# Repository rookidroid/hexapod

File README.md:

#  Hexapod

A family of 18-DOF, 3D-printed hexapod robots powered by an ESP32. Walk them from your phone over WiFi, or stream poses to them live from a computer. All the robots run the same firmware and gait generator. What differs is their frame, servos and dimensions.

## The Robots

| | [Nougat](./robots/nougat/) | [Mochi](./robots/mochi/) | [Macaroon](./robots/macaroon/) |
|---|---|---|---|
| |  |  |  |
| **Servos** | 18 × 21G digital | 18 × MG92B micro | 18 × 25 kg digital |
| **Battery** | 2 × 18650 (2S1P) | 2 × 18650 (2S) | 4 × 18650 (2S2P) |
| **Leg links** (coxa / femur / tibia) | 38 / 54 / 97 mm | 36 / 44 / 85 mm | 62 / 76 / 132 mm |
| **Controller** | ESP32 (Pico W legacy) | ESP32 (Pico W legacy) | ESP32 |
| **Firmware define** | `ROBOT_NOUGAT` | `ROBOT_MOCHI` | `ROBOT_MACAROON` |
| **WiFi SSID** | `hexapod_nougat` | `hexapod` | `hexapod_macaroon` |

Each robot's folder has its full build guide: bill of materials, 3D-printed parts, assembly, software setup, calibration and troubleshooting.

## Repository Layout

```text
hexapod/
├── robots/                 # Hardware for each robot
│   ├── nougat/             #   README (build guide), 3d print/, images/
│   ├── mochi/
│   └── macaroon/
├── images/                 # Images shared by all robots
└── software/
    ├── hexapod_esp32/      # ESP32 firmware (Arduino sketch), shared by all robots
    │   ├── robot.h         #   Pick the robot you are building here
    │   └── src/robots/     #   Per-robot settings and generated motion tables
    ├── package_esp32.py    # Packages the ESP32 sketch into one copy per robot
    ├── hexapod_pico/       # Legacy Raspberry Pi Pico firmware (unmaintained)
    └── path_tool/          # Gait generator that produces the motion tables
        └── robots/         #   Per-robot geometry and gait parameters (JSON)
```

## Quick Start

1. Build the robot by following its guide in [`robots/`](./robots/).
2. Open [`software/hexapod_esp32/hexapod_esp32.ino`](./software/hexapod_esp32/hexapod_esp32.ino) in the Arduino IDE.
3. In [`robot.h`](./software/hexapod_esp32/robot.h), leave only your robot's `#define ROBOT_*` uncommented.
4. Upload, join the robot's WiFi network and calibrate it at `http://192.168.4.1`.

To skip step 3, download `hexapod_<robot>_<version>.zip` from the [releases](https://github.com/rookidroid/hexapod/releases): a copy of the sketch with your robot already selected. `python software/package_esp32.py` builds the same zips locally into `dist/`.

The [ESP32 firmware README](./software/hexapod_esp32/README.md) covers setup, the UDP protocol and OTA updates. The [path tool README](./software/path_tool/README.md) explains how the motion tables are generated and how to add a new robot.

## License

[GPL-3.0](./LICENSE)

## Support

- Website: [rookidroid.com](https://rookidroid.com/)
- Issues: [GitHub Issues](https://github.com/rookidroid/hexapod/issues)
- E-mail: [info@rookidroid.com](mailto:info@rookidroid.com)

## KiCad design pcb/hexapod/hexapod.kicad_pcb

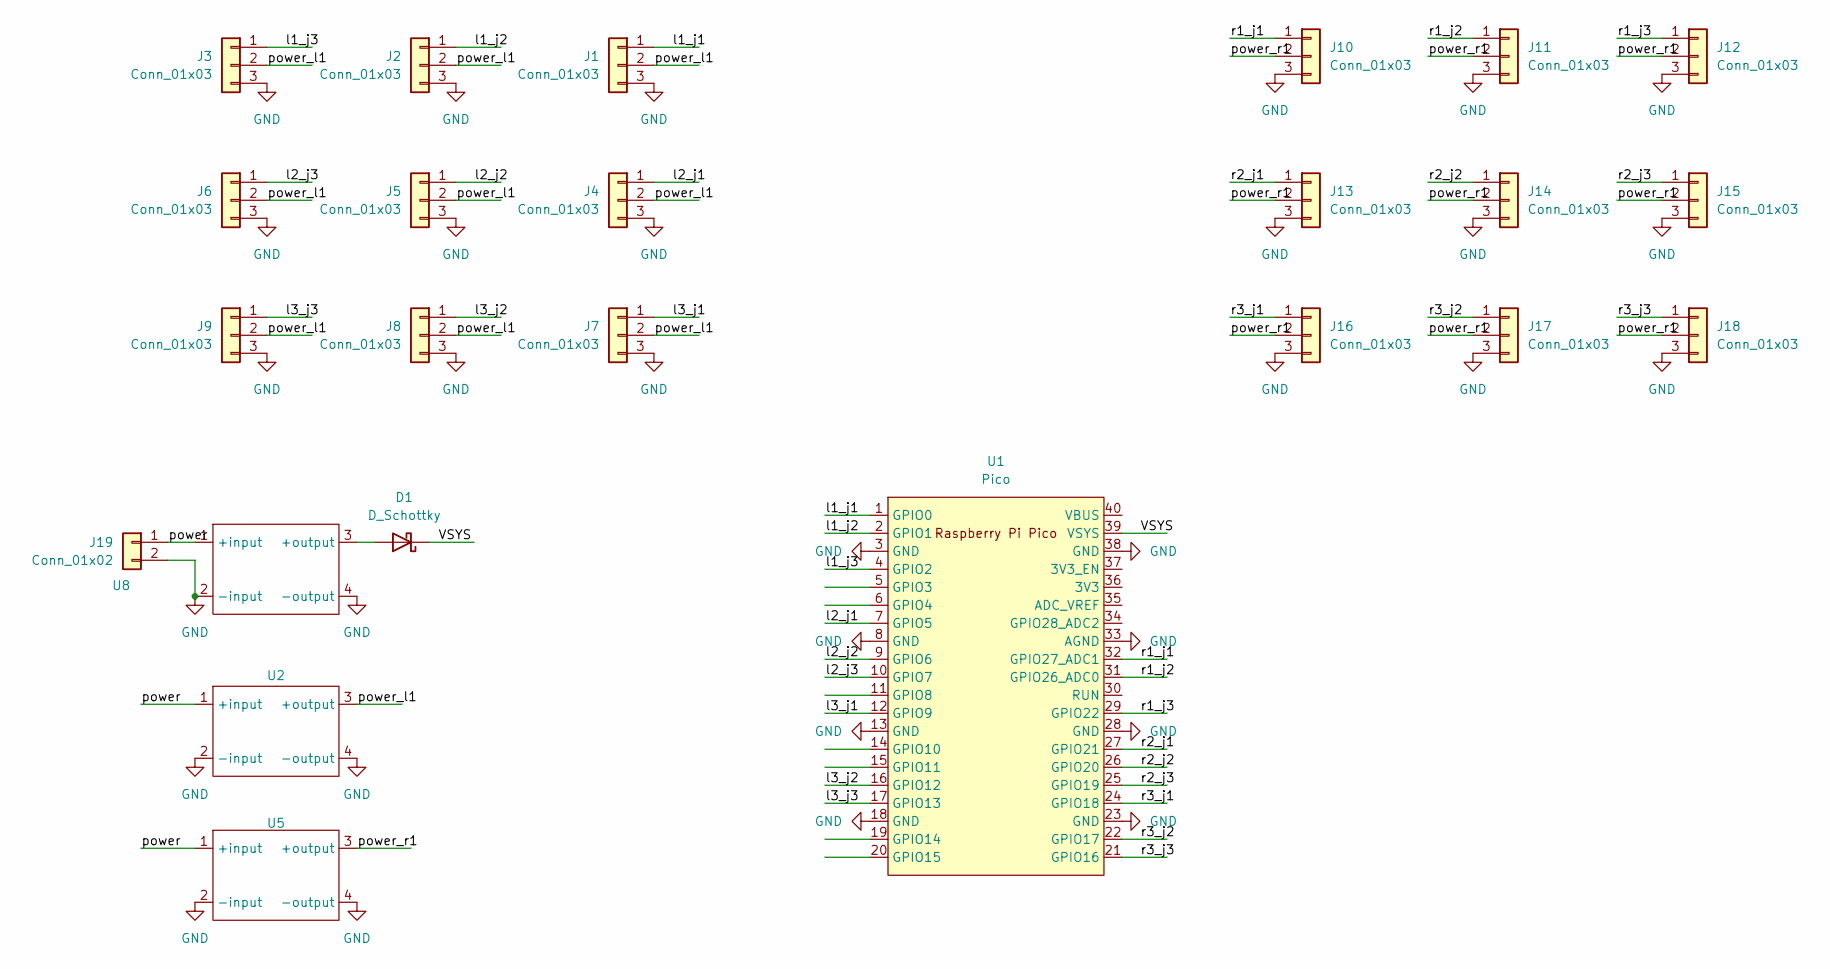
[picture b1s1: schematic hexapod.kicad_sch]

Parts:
D1: D_Schottky; D_T-1_P10.16mm_Horizontal
J1, J2, J3, J4, J5, J6, J7, J8, J9, J10, J11, J12, J13, J14, J15, J16, J17, J18: Conn_01x03; PinHeader_1x03_P2.54mm_Vertical
J19: Conn_01x02; TerminalBlock_MaiXu_MX126-5.0-02P_1x02_P5.00mm
U1: Pico; RPi_Pico_SMD_TH
U2, U5: XL4005
U8: Mini360

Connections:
/VSYS: D1.1 (K), U1.39 (VSYS)
/l1_j1: J1.1, U1.1 (GPIO0)
/l1_j2: J2.1, U1.2 (GPIO1)
/l1_j3: J3.1, U1.4 (GPIO2)
/l2_j1: J4.1, U1.7 (GPIO5)
/l2_j2: J5.1, U1.9 (GPIO6)
/l2_j3: J6.1, U1.10 (GPIO7)
/l3_j1: J7.1, U1.12 (GPIO9)
/l3_j2: J8.1, U1.16 (GPIO12)
/l3_j3: J9.1, U1.17 (GPIO13)
/power: J19.1, U2.1 (+input), U5.1 (+input), U8.1 (+input)
/power_l1: J1.2, J2.2, J3.2, J4.2, J5.2, J6.2, J7.2, J8.2, J9.2, U2.3 (+output)
/power_r1: J10.2, J11.2, J12.2, J13.2, J14.2, J15.2, J16.2, J17.2, J18.2, U5.3 (+output)
/r1_j1: J10.1, U1.32 (GPIO27_ADC1)
/r1_j2: J11.1, U1.31 (GPIO26_ADC0)
/r1_j3: J12.1, U1.29 (GPIO22)
/r2_j1: J13.1, U1.27 (GPIO21)
/r2_j2: J14.1, U1.26 (GPIO20)
/r2_j3: J15.1, U1.25 (GPIO19)
/r3_j1: J16.1, U1.24 (GPIO18)
/r3_j2: J17.1, U1.22 (GPIO17)
/r3_j3: J18.1, U1.21 (GPIO16)
GND: J1.3, J2.3, J3.3, J4.3, J5.3, J6.3, J7.3, J8.3, J9.3, J10.3, J11.3, J12.3, J13.3, J14.3, J15.3, J16.3, J17.3, J18.3, J19.2, U1.3 (GND), U1.8 (GND), U1.13 (GND), U1.18 (GND), U1.23 (GND), U1.28 (GND), U1.33 (AGND), U1.38 (GND), U2.2 (-input), U2.4 (-output), U5.2 (-input), U5.4 (-output), U8.2 (-input), U8.4 (-output)
unnamed: D1.2 (A), U8.3 (+output)

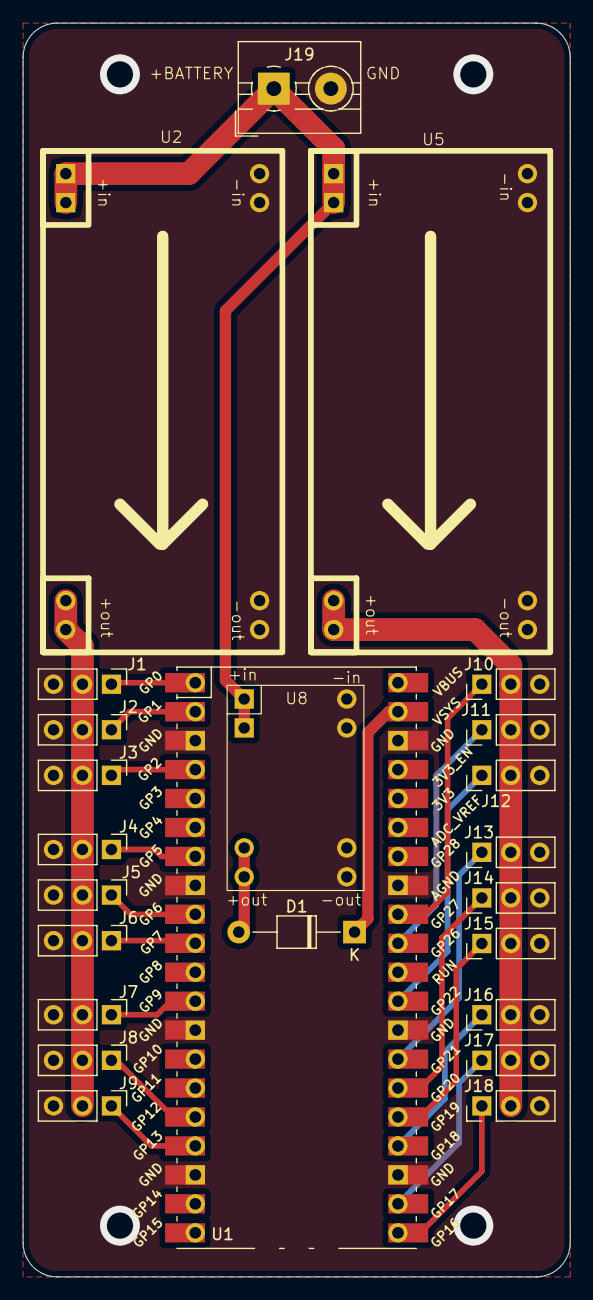
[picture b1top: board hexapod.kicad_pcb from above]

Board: 2 copper layers, 48.0 x 110.0 mm, 24 parts (0 on the bottom side), 24 nets.

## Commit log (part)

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2024-06-20 update path generator
2024-07-02 move configurations to config.h
2024-07-02 rename
2024-09-11 v1.0
2024-09-24 adjust leg for MG90S
2024-09-28 update lut for the leg adjustment
2024-10-04 update instruction
2024-10-05 update docs
2024-10-07 photo of mg90s
2024-10-13 #1 Correct schematic mistakes
2024-10-14 #2 Improve readme for mirrored joints and feet
2024-11-10 remove android
2024-12-17 pcb design
2024-12-18 change default IP
2024-12-18 gerber file for fab
2024-12-29 remove old stl
2025-01-03 update Mini360 pad
2025-01-05 fix pcb
2025-01-11 move pcb to another repo
2025-02-22 add body models
2025-02-22 adding foot and joint model files
2025-02-22 add leg model files
2025-02-22 update gifs
2025-02-22 add diagram
2025-02-22 add servo image
2025-02-23 add controller boards
2025-02-24 update diagrams
2025-02-24 add photos
2025-02-24 improve images
2025-02-24 remove photos
2025-02-25 new images
2025-03-01 update photos
2025-05-29 add a flag to set calibration mode
2025-11-23 Refactor hexapod initialization and command parsing
    Improves code organization by extracting UDP command parsing into a dedicated function, adds helper for setting all servo positions, and introduces constants for hardware configuration. Enhances seri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
2025-11-23 Delay boot sequence until WiFi client connects
    The boot-up motion now waits for a WiFi client to connect before executing. This ensures the hexapod only starts its boot sequence when a client is present, and allows OTA updates during the wait. If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
2025-11-24 Refactor formatting and improve code consistency
    This commit updates spacing, indentation, and formatting throughout hexapod_esp32.ino for improved readability and consistency. No functional changes were made; only code style and formatting adjustm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
2025-11-24 Refactor motion command handling with unified config
    Introduced a MotionConfig struct and array to unify motion command mapping and LUT selection. Replaced repetitive if-else chains in loop() and parseCommand() with table-driven lookups, improving main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
2025-11-24 Add detailed comments and structure to hexapod_esp32.ino
    Improved code readability by adding descriptive comments, section headers, and clarifying variable purposes throughout the hexapod_esp32.ino file. Enhanced documentation for motion configuration, har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
2025-11-24 Refactor motion mode handling to use indices
    Removed MotionMode enum and updated motion configuration to map commands directly to LUTs using table indices. Simplified motion state tracking and execution logic by replacing enum-based selection w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
2025-11-24 Expand and update hexapod ESP32 README
    README now includes detailed setup instructions, hardware requirements, feature overview, UDP command reference, OTA update steps, troubleshooting, and guidance for adding custom motions. This improv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
2025-12-29 Add Bambu Studio 3MF files for body, foot, joint, and leg
    Renamed 'body.3mf' to 'bambu_studio_body.3mf' and added new 3MF files for foot, joint, and leg components, all intended for use with Bambu Studio.
2025-12-29 Update 3D print parts list and hardware specs in README
    Revised the 3D-printed parts table to reflect updated part names, quantities, and images. Removed redundant print orientation notes and accessory section. Updated hardware specifications for screws a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
2025-12-29 Revise and expand README with detailed build instructions
    Enhanced the README with clearer feature descriptions, a comprehensive bill of materials, detailed assembly steps, and expanded software setup instructions for both ESP32 and Raspberry Pi Pico. Added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
2025-12-29 Update assembly_body.gif image
    Replaces the existing assembly_body.gif with a new version. This may reflect updated visual content or corrections to the image.
2025-12-29 Update assembly GIF images
    Replaced or modified assembly_foot.gif, assembly_joint.gif, assembly_leg.gif, and assembly_whole.gif with new versions to reflect updated visuals or corrections.
2025-12-29 Update hexapod model SVG with new dimensions and image
    Increased the SVG canvas size and updated the embedded image and metadata. This change reflects a new export from Inkscape, likely to improve image quality or fit updated content.
2025-12-29 Update hexapod model image
    Replaced the existing hexapod_model.jpg with a new version. This may reflect updated visuals or corrections to the model image.
2025-12-29 Update servo reference and image in README
    Replaced the 21G servo with the MG92B servo in the parts list, updated the image accordingly, and removed the old servo image.
2025-12-29 Update assembly_whole.gif image
    Replaced the existing assembly_whole.gif with a new version. This may reflect updated visual content or corrections in the image.
2025-12-29 Revise and expand setup and usage instructions in README
    Updated the README to clarify and expand setup steps for both ESP32 and Raspberry Pi Pico, including detailed library requirements, board configuration, and WiFi/OTA instructions. Added explicit UDP 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
2025-12-29 Update hexapod logo images
    Refreshed hexapod-logo.png and hexapod-logo.svg with a new design and updated SVG structure, including new shapes, colors, and layout. The SVG now uses a different Inkscape version and features a mor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
2025-12-29 Update switch type and image in README
    Changed 'Rocker Switch' to 'Toggle Switch' in the parts list, updated specifications, and replaced the switch image to match the new description.
2025-12-29 Update servo tick conversion rate in README
    Corrected the servo angle-to-tick conversion guidance from '1° ≈ 10 ticks' to '0.44° ≈ 1 tick' for improved accuracy in calibration instructions.
2025-12-30 Update reference image captions in README
    Changed the captions for the reference images in the calibration section to improve clarity. 'Front View - Check coxa and femur alignment' is now 'Front View', and 'Side View - Check all three joints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
2025-12-30 Update PCB diagram images for ESP32 and Pico
    Refreshed both JPG and SVG files for ESP32 and Pico PCB diagrams. SVG files show updated Inkscape metadata and possible diagram adjustments.
2025-12-31 Fix right leg offset tick value in config
    Corrected the right_offset_ticks value for the first leg from -10 to 10 to address installation error compensation.
2026-01-12 Update right leg offset ticks in config.h
    Adjusted the right_offset_ticks array to correct installation error values for the hexapod ESP32 configuration. Also updated the 3D print file for the Bambu Studio foot.
2026-01-17 Update 3D body parts and add 18650 battery holder
    Added a new 18650 battery holder (2S2P) STL file. Updated several body, foot, joint, and leg STL files. Removed obsolete body_battery.STL and body_head.STL files to reflect design changes.
2026-01-29 Add body_battery.STL 3D model file
    Added a new STL file for the body battery component in the 3D print/body directory.
2026-02-01 Update 3D prints and adjust servo offsets
    Replace binary 3MF/STL assets for foot and body side, and update hexapod calibration offsets. In software/hexapod_esp32/config.h the left_offset_ticks and right_offset_ticks were changed from all zer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
2026-02-01 Tune gait LUTs; enable boot sequence; bump delay
    Update walk lookup tables and tooling, enable boot-up/motion execution, and slow servo updates.
    - Increase DELAY_MS from 10 to 30 in software/hexapod_esp32/config.h to reduce servo update frequency.
    - Re-enable boot sequence and motion execution in software/hexapod_esp32/hexapod_esp32.ino (restore boot handling and exec_motion); comment out posture_calibration call.
    - Revise numerous gait LUT entries in software/hexapod_esp32/motion.h (walk_0, walk_180, walk_r45, walk_r90) to tune walking profiles.
    - Update corresponding path_tool files (config.json, lut_generator.ipynb, motion.h) to keep the LUT generation and tooling in sync.
2026-02-01 Add web calibration UI and EEPROM storage
    Introduce a web-based calibration interface and persistent EEPROM storage for servo offsets. Adds WebServer and EEPROM includes, EEPROM layout/constants and load/save helpers, and integrates EEPROM i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
2026-02-01 Add web calibration UI and EEPROM offsets
    Add on-device calibration support: include WebServer and EEPROM, introduce EEPROM layout/constants and functions to load/save servo offset ticks. Replace hardcoded non-zero offsets in config.h with z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
2026-02-01 Update UI theme, layout tweaks and footer
    Revamp the web UI styles: replace cyan accents with purple tones (titles, buttons, borders, status), adjust button colors/hover, increase input width, tweak spacing (leg-grid gap, leg-column gap, joi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
2026-02-01 Reduce servo delay and zero servo offsets
    Adjust config.h to speed up servo updates by changing DELAY_MS from 30 to 20. Also reset left_offset_ticks and right_offset_ticks to all zeros to remove previous calibration offsets and neutralize se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
2026-02-01 Revamp web UI and calibration flow
    Update the hexapod web UI styling and streamline the calibration workflow. Changes include: revised color palette (purple accents), updated button styles and hover states, increased input widths, adj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
2026-02-02 Add web-based calibration interface and update calibration instructions
2026-02-03 Remove LEGO images and update photos
    Delete obsolete LEGO images and remove their references from README. Replace two photo assets with updated versions (images/hexapod_photo.jpg and images/hexapod_photo_battery.jpg) to refresh project 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
2026-02-03 Update README: remove v1 warning and enlarge images
    Remove the strong recommendation to start with Hexapod v2 and the warning about unreliable MG90S servos used in Hexapod v1. Also increase the displayed image widths from 300 to 400 for better visibil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
2026-03-15 Tweak servo delay and calibrate LUT values
    Increase servo update delay and apply many small numeric calibrations to lookup tables used for gaits and maneuvers. Changes: software/hexapod_esp32/config.h (DELAY_MS 10 -> 12), numerous value adjus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
2026-03-15 Update hexapod gait LUTs and generator
    Adjust lookup tables for walking motions across multiple orientations (walk_0, walk_180, walk_r45, walk_r90, walk_r135) in software/hexapod_esp32/motion.h and the corresponding motion.h in software/p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
2026-03-15 Add body_head.STL and update Bambu 3MF
    Add new 3d print/body/body_head.STL model and update the existing 3d print/bambu_studio_body.3mf project file (binary) to reflect the change. This adds the head part to the print assets and updates t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
2026-03-16 Adjust servo delay and trim motion LUTs
    Increase servo update delay (DELAY_MS) from 20 to 25 ms and simplify motion lookup tables. The change modifies lut_walk_0 entries and removes several direction-specific LUT arrays to reduce duplicate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
2026-03-17 Update 3D print model files
    Replace binary 3D assets: updated body/body_head.STL and hexapod_mochi.3mf. These changes refresh the printed model geometry/exports for the body head and the full hexapod assembly; no source code or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
2026-03-20 Update fastwalk LUTs and generator params
    Regenerated and updated the fast walk lookup tables (lut_fast_forward and lut_fast_backward) in software/hexapod_esp32/motion.h and software/path_tool/motion.h with new coordinate values for the 28-s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
2026-04-20 Replace body_battery STL with 3MF
    Remove the body_battery.STL file and add a new body_battery.3mf file. This switches the 3D model from STL to 3MF format (preserving richer metadata and modern slicer features).
2026-05-23 Add web calibration, EEPROM and motion refactor
    Introduce a web-based servo calibration UI and persistent EEPROM storage; refactor motion handling and hardware initialization. Changes include: add WebServer and EEPROM support, a calibration HTML/J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
2026-06-01 Change default WiFi SSID to hexapod_macaroon
    Update software/hexapod_esp32/config.h to change the default APSSID from "hexapod" to "hexapod_macaroon". The APPSK remains unchanged. This makes the device SSID more specific/identifiable.
2026-06-14 new logo

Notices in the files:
README.md:
License: GPL v3
